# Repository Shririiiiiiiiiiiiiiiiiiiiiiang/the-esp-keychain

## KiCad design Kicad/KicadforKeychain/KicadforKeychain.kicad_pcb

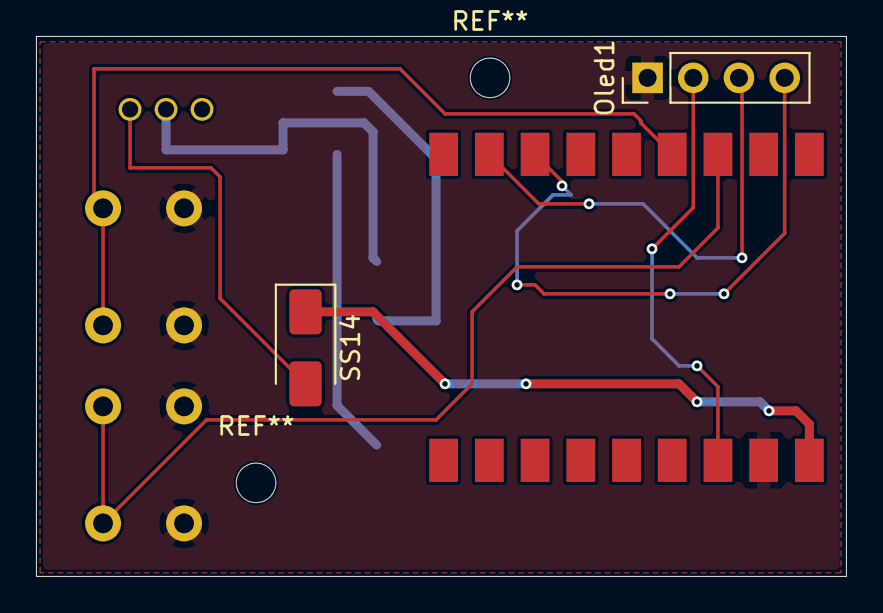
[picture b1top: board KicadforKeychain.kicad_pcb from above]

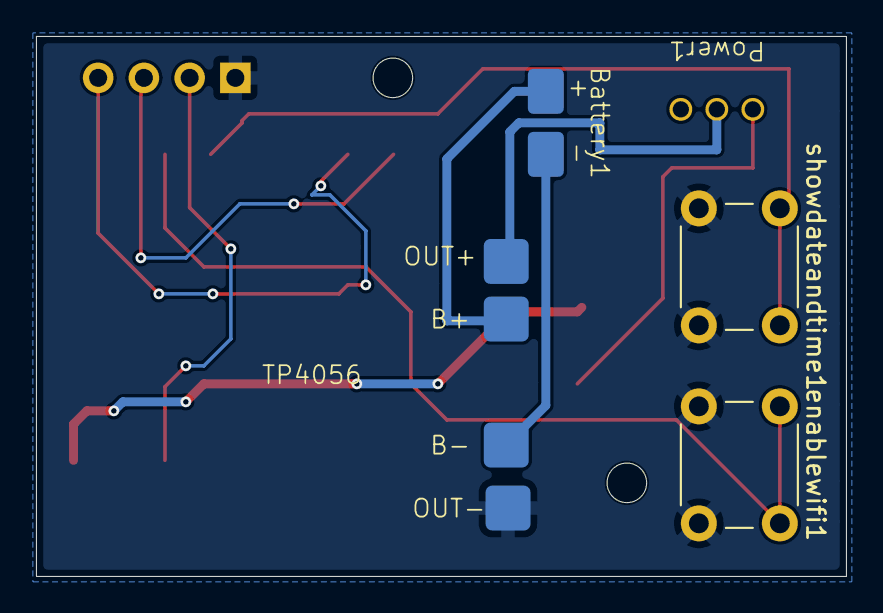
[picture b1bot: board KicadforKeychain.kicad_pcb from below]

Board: 2 copper layers, 45.0 x 30.0 mm, 8 parts (5 on the bottom side), 11 nets.

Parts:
Battery1: Conn_01x02_Pin; Battery
ESP32S3supermini1: ESP32S3mini
Oled1: Conn_01x04_Socket; PinHeader_1x04_P2.54mm_Vertical
Power1: SW_SPDT; slideswitch
SS14: D_Schottky; D_SMA
TP4056: Conn_01x04_Pin; tp4056
enablewifi1: SW_Push; SW_PUSH_6mm
showdateandtime1: SW_Push; SW_PUSH_6mm

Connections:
/3V3: ESP32S3supermini1.16 (3V3), Oled1.2
/5V: ESP32S3supermini1.18 (5V), SS14.1 (K)
/GND: ESP32S3supermini1.17 (GND), Oled1.1, TP4056.4, enablewifi1.2, showdateandtime1.2
/SCL: ESP32S3supermini1.2 (GPIO6), Oled1.3
/SDA: ESP32S3supermini1.3 (GPIO5), Oled1.4
/VBAT+: Battery1.1, TP4056.1
/VBAT-: Battery1.2, TP4056.2
/VOUT: Power1.2 (B), TP4056.3
/VSWITCH: Power1.1 (A), SS14.2 (A)
/datetimebtn: ESP32S3supermini1.6 (GPIO2), showdateandtime1.1
/wifibtn: ESP32S3supermini1.7 (GPIO1), enablewifi1.1
